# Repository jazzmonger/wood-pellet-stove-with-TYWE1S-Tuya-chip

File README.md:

Wood Pellet Stove with Tuya TYWE1S chip flashed with ESPHome gives you COMPLETE local control over ALL stove functions (and adds some).

> **No soldering, no flashing, no stove downtime:** if you just want local Home Assistant control (power, set temp, P1–P4, ECO1/ECO2, temperatures, decoded faults) without the vendor app, see **[docs/LOCAL-CONTROL.md](docs/LOCAL-CONTROL.md)**. It keeps the stock TYWE1S firmware and uses the [tuya-local](https://github.com/make-all/tuya-local) integration with the ready-made stove profile in [`tuya-local/`](tuya-local/pellet_stove_tywe1s.yaml). The ESPHome flashing and ESP32 mods below remain the way to unlock ultra-low burn, PID auger control, real-time temps and remote error reset.

The Discussions section also has LOTs of info: https://github.com/jazzmonger/wood-stove-with-TYWE1S-Tuya-chip/discussions
Including the discussion of a new circuit board design.

This project dives deep into the TuyaMCU parts of ESPHome that can be used to control various Tuya cloud based pellet stoves.  While the ESPHome TuyaMCU implementation is mostly robust, getting information on what it does and how it does it and why has been challenging to say the least.  I hope this helps someone else. I now have two of these stoves running ESPHome and FINALLY they function the way I want them to, not how some idiotic low-budget coder tried to program them.  I used to wake up cursing my pellet stoves.  Now I just wake up all warm and fuzzy.

The Advanced version completely replaces the Tuya Wifi module with an ESP32 D1 Mini chip and adds a whole new world of control to these stoves.

TuyaMCU Docs: https://esphome.io/components/tuya.html

The Tuya TYWE1S chips and those like it are basically just repackaged ESP8266 modules.  All the functions of the 8266 are all there.  The TuyaMCU libray in ESPHome provides an abstraction layer between the display/control module and Home Assistant. It allows control messages to be both Sent and Received from the device the module is controlling. In this case, our stove's main brain/control unit, or MCU as its called.

I'm an electronic engineer/designer by education and training, not a professional programmer, but thankfully ESPHome makes all this pretty easy. That said, I LOVE hacking this stuff, so  start with replacing the buggy, error prone Tuya control software by flashing ESPHome onto the display's TYE1S Tuya communications & controller chip.

**Product Models:** 
Cleveland Ironworks Wood Pellet Stove (there are 4 models, all use the same controller).  
https://www.cleveland-ironworks.com/products/pellet-stoves.html
I have a test bench set up with a spare control board. i have 2 models of this stove which both fail, but for different reasons.

It also appears from the Wifi module (N12210) that this exact same controller is used in Nemaxx Pellet Stove Pellet Heater P6 P9 P12.  https://www.ebay.com/itm/193755684864

Masterforge has the exact same models of this stove, all will use the same controller.

There are several others sold by Lowes, and other retailers that use the same display control board and TYWE1S chip.

There are a few displays that look slightly different but I believe all have the same basic internals. The displays have exactly the same function, just dufferent color faceplates. if they look like any of these then youre in luck!
All will have a TYWE1S chip that provide wifi functions that can be reprogrammed with ESPHome.

UPDATE: if the chip is the blue D1 Mini on the daughterboard, and the app you use is "Fire@home" and you got the stove in the EU, the stove uses the Blynk protocol, not Tuya.  We've exhausted all options trying to get this working. see the discussions. I would need the actual display board from this stove to decode the protocol being used

The wood stoves work ok some of the time, but the stove malfunctions fairly frequently.  
Common mafunctions include:
- randomly turning off w/ the msg "Goodbye!" on the display.
- pellets failing to light in the hopper
- not coming back on after power failure
- various cryptic E messages from time to time. E1,E2,ESC1, ESO1,ESC2,ESO2,etc  
- the stove will overheat when set to ECO2 and P1, throwing ESC1 errors. mitigate this with a fan behind the stove, triggered by exhaust temp.  set combustion fan to -10 for P1 in stove settings. 
Putting a fan behind the stove also fixes E6 error code indicating the temp sensor below the pellet hopper is reading too high

**Basic Problem Definition**
Pellet stoves made by Cleveland Ironworks all use the TuyaMCU chip TYWE1S to communicate with the stove's MCU inside the display unit.  Their shoddy programmer defined multiple datapoints for the same attribute in at least 2 cases, the most important being temperature.  This results in the Tuya integration reporting a random (usually negative) false value for current temp. The other problem is it sends its temp values as degrees F and ALL esphome climate entities originate in C.  If you set your HA instance to imperial, it will automagically convert C to F.  In this case it convering what it thinks is C ( but is really F) into F again.  temp readings are whacked and there was nothing you can do until now.

link to product manual https://www.cleveland-ironworks.com/mwdownloads/download/link/id/2763

Their app is a vendor written Tuya based app that looks like this:

Simply flashing esphome to the chip gives incorrect temp readings due to the stove using F instead of C for values. a fix for this is coming (update: its fixed).  The stove below might work great in purgatory (which, Im sure, is where these stoves were built), but not in the real world...

also, the main problem with trying to control the stove by brute force by manually controlling everything in ESPHome is setting your target temp doesn't work bc it fights with the stove's internal "set temp" that is set thru the front panel. when the room temp sensor reaches the user set value it shuts off to stove - its all a self contained system. The daughterbiard w/ the TYWE1S is only there to provide wifi support.  There there is no way to convert the stove control fully to to ESPHome. too many sensors, blowers, igniters, relays and safety issues to etc to deal with. This is all best left to the dusplay and main MCU control board. But we can secretly (and safely) intervene...

**Solution**
- Flash ESPHome to the TWYE1S daughterbiard chip using TuyaMCU. This is the module that normally relays info to and from the stoves control board and also provides a WiFi control interface to the Tuya iOT China based cloud platform. ESPHome eliiminates China from the equation and gives you local, Home Assistant control.
- use the new mod I got one of the ESPhome devs to make for me and you're golden.  its defined in the esphome config file.
- if your stove is turning off for no reason w/ "Goodbye" displayed on the screen, then the automations I've provided should help mitigate this
- go a step further and make a few *very* simple mods to the display and control board and you get FULL control over this stove WITHOUT sacraficing any of the safety features built into this stove.

See the Discussions for specific solutions to some of the errors and problems I've solved over the past year of doing battle with this stove. Its in the Discussions where I show the deep mods that are available and really make this Pellet Stove shine.

Post a message in the Discussions for basic questions or create a PR (problem report) if you are doing mods to your stove and run into issues.  I've tried to be as complete as possible and probably seen every problem these stoves have and then some.
Have fun!

**Data Points used by TuyaMCU and Tuya cloud:**
```
1 - Power on (Heat)
4 - Mode P1/P2/P3P4
101 - ECO1/ECO2
104 - Error Code
105 - random, unused
106 - Set desired room Temp
107 - Current Temp
108 - Pipe Temp
109 - Protect Temp
```
Error code is dp 104 (these come back from the server as numbers and are then mapped to error codes in the vendor app).  See my sensors.yaml file for how to decode them.

*Flashing the chip*
Carefully remove it from the display module.  It unplugs easily. or leave it in the display and use the power from the display to power the chip.  Ive done it both ways, either is fine.

this link shows you how to do it: https://tasmota.github.io/docs/TuyaMCU-Devices/#costco-charging-essentials

EDIT: for future reference, if unplugging the module from the display, I used 3.3v from the FTTD adapter to power the TYWE1S, U0TX (goes to RX on the FTTD adapter)  and U0RX (goes to TX on the FTTD adapter) then I only grounded GPIO0 at bootup to flash the chip.  Remove this ground from GPIO0 after its flashed and restart the chip. Also, connect 3.3V (not 5v) to the 3V3 pin on the TYWE1S chip, pin 4, or just leave the module plugged in and use the stove to power the chip.

WARNING - be careful when you solder wires to the board/chip to flash the chip.  I used breadbord wires w/pins and my VCC connection broke at some point and it took most of the circuit board trace off both the board AND the chip.  I salvaged it with a Frankenstein jumper, but you've been warned! Just be careful when handlin, use long wires and you should be fine.

The spiffy new entity with options to change Power and ECO mode. See the file uploads for all the code to generate these.

Special cards used frim HACS
type: custom:slider-entity-row
type: custom:plotly-graph

My "Ultimate" Pellet Stove Command Module after completely replacing the wifi module and Tuya chip with an ESP32 D1 mini. Yes, it can be done.

Another piece of the puzzle was to snoop on the RX UART line going from the display to the MCU control board.  this lets you echo messages from the display to home assistant as there is no other way to do it. its a little flakey at times (its just display messages), but mostly works. See the discussions section on how i achieved this bit of UART magic!

And finally, while i have had the stove burn for 2-3 days straight, it does go out if the ultra-low burn pot settings arent just right.  So, in the "Ultimate vesion" I add a wire to monitor the UART messages from the main MCU that contain temp updates so I can measure realtime temp updates (instead of at 1 min intervals via the Tuya crap). This helps to better control the burn pot and keep the fire from going out when on "Ultra Low" setting. Again, see Discussions for more info.

Build and use at your own risk!

I will not be responsible for any damages including but not limited to: errors or omissions, loss of life, or property damage. You have been warned.

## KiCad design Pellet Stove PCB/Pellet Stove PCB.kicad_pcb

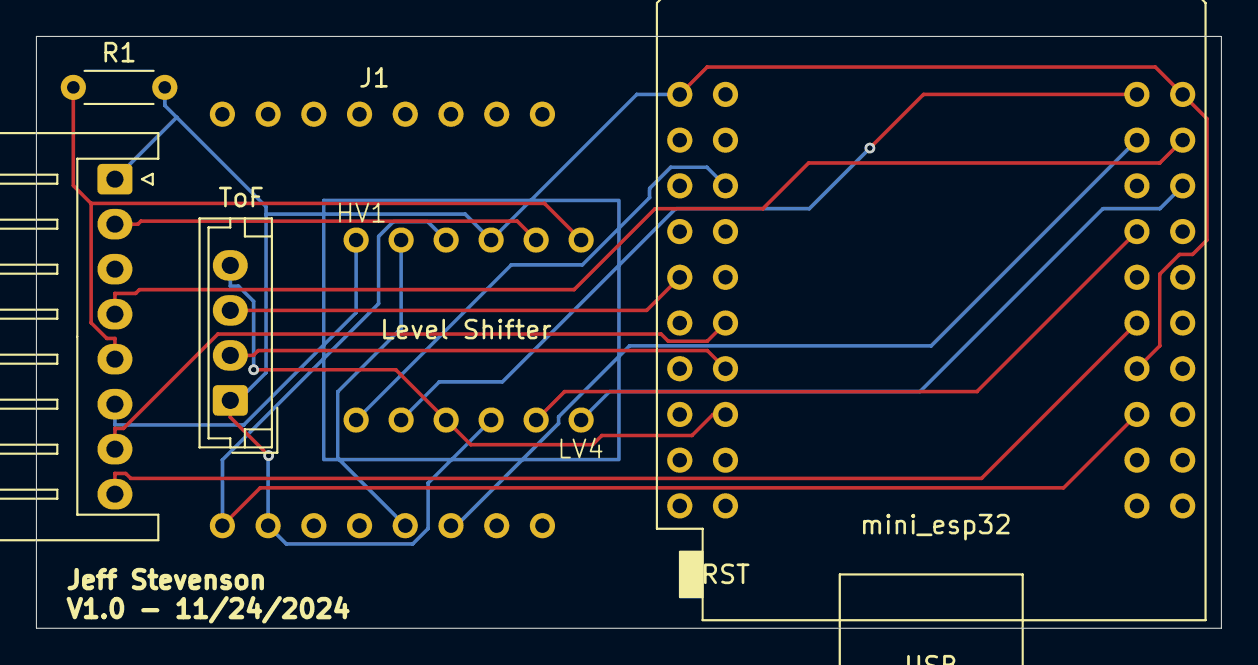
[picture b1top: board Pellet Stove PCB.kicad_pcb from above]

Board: 2 copper layers, 65.8 x 32.9 mm, 6 parts (0 on the bottom side), 17 nets.

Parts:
J1: Pellet Stove Header pins
J2: Logic Level Converter
J4: MCU USB & display; JST_XH_S8B-XH-A_1x08_P2.50mm_Horizontal
J6: ToF; JST_EH_B4B-EH-A_1x04_P2.50mm_Vertical
R1: 1k; R_Axial_DIN0204_L3.6mm_D1.6mm_P5.08mm_Horizontal
U1: mini_esp32; ESP32_mini

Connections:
GND: J1.10, J2.4 (GND), J2.9 (GND), J4.1, J6.1, R1.2, U1.1 (GND), U1.22 (GND), U1.33 (GND)
unnamed: J2.3 (3.3v), J6.4, U1.16 (3V3)
unnamed: J2.12 (HV1), J4.6
unnamed: J1.13, J2.11 (HV2)
unnamed: J2.8 (HV3), J4.2
unnamed: J2.7 (HV4), J4.5, R1.1
unnamed: J1.9, J2.10 (HV), U1.35 (VCC_(USB))
unnamed: J2.1 (LV1), U1.6 (IO_26/D0)
unnamed: J2.2 (LV2), U1.21 (TXD)
unnamed: J2.5 (LV3), U1.27 (IO_21/D2/SDA)
unnamed: J2.6 (LV4), U1.26 (IO_25)
unnamed: J4.4, U1.24 (IO_27)
unnamed: J4.7, U1.12 (IO_23/D7)
unnamed: J4.8, U1.31 (IO_16/D4)
unnamed: J6.2, U1.14 (IO_05/D8)
unnamed: J6.3, U1.9 (IO_33)
unnamed: J1.14, U1.23 (RXD)

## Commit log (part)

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2022-12-06 Add files via upload
    Various automations to add functionality to the pellet stove.
2022-12-06 Add files via upload
    Sensor.yaml file containing sensor definitions referenced in automations and Lovelace cards
2022-12-06 Add files via upload
    Cards to display pellet stove and debug all aspects
2022-12-21 Add files via upload
    Modifications to add new P5 power level that modifies Auger feed rates. Requires modifying both the display board and MCU board
2022-12-22 README File
2022-12-23 Adds new Power Level 5. NOTE: requires mods to MCU board
    config file that adds a Power Level P5 that is fully configurable while in ECO2 mode.
    The hope is this will turn down the heat slightly so the stove goes thru fewer on/off cycles and just maintains a heat adjust so the room just cools slightly. ECO2 mode will kick back to "Heating" wh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
    Requires MCU and Display board simple mod. See discussions
2022-12-23 adds sensors for wood pellet stove
2022-12-23 Various automations to manage pellet stove. names will need changing!
    I have 3 of these stoves, one dev, house, shop. my dev stove is on my workbench.
2023-01-11 Add files via upload
    #adds a Power Level P5 that is fully configurable while in ECO2 mode.
    #adds echo of actual display messages and status via MCU UART monitoring
    #
    #These mods will turn down the heat slightly during idle mode so the stove goes thru fewer
    #on/off cycles and just maintains a lower heat setting
    #so the room just cools slightly. when room cools, ECO2 mode will kick back to "Heating" which
2023-01-11 New power level P5. REQUIRES MODS!
    #adds a Power Level P5 that is fully configurable while in ECO2 mode.
    #adds echo of actual display messages and status via MCU UART monitoring
    #
    #These mods will turn down the heat slightly during idle mode so the stove goes thru fewer
    #on/off cycles and just maintains a lower heat setting
    #so the room just cools slightly. when room cools, ECO2 mode will kick back to "Heating" which
2023-01-21 Latest files
2023-01-21 Create new power level P5. Requires mods to Display/control bd
2023-01-28 Update and rename lovelace cards.yaml to lovelace cards(with all mods).yaml
    You need all my mods for these cards to function
2023-01-28 Basic Pellet Stove Lovelace card
    Use this with basic pellet stove , no physical mods.
    All Sensor names assume you use the following naming conventions in ESPHome config file:
    substitutions:
    device_name: "house-wood-pellet-stove"
    device_description: House Wood Pellet Stove running ESPHome
    friendly_name: House Wood Pellet Stove
2023-01-28 Basic Lovelace Pellet stove card (no mods)
2023-01-28 Lovelace card (with all physical stove mods)
    You must do all physical mods to the stove for these cards to work
2023-01-28 Various basic pellet stove automations
2023-01-28 Basic ESPHome config file (no physical mods)
2023-01-28 Pellet Stove Sensor entries
    Add these sensors to your sensor.yaml file
2023-01-28 configuration.yaml entries for binary_sensors
    add these binary sensors to your configuration.yaml file
2023-03-17 D1 Mini ESP32 firmware replaces entire Wifi daughter board
2023-03-17 Lovelace Command Center Dashboard - ESP32 version
2023-03-17 Sensor.yaml entries for Pellet stove
2023-04-10 ESP32 chip replaces TYWE1S
    Plus this adds a TON of features
2024-11-23 Pellet Stove PC Board KiCad design files, Symbols & Footprints
2025-01-05 ESP32 Pellet Stove with mods.yaml
2025-01-05 not relevant
2025-01-05 Basic ESPHome config file for wood pellet stove.yaml
2025-02-17 PID Version of Ultimate contoller.
    PID Version of Ultimate contoller.
2025-02-17 PID version of Modified Pellet Stove
    Auger mod on the main board is now corolled a low temps by a PID controller.
2025-11-02 Rename ESPHome config file for wood pellet stove.yaml to ESPHome basic config file fot TYWE1S chip flash.yaml
2025-11-15 Wood Pellet Stove Basic Config using ESP32
    Requires my pellet stove circuit board and an ESP32 to use this file
    # No mods to the pellet stove control board are required
    # Adds local sensors for all attributes previously in Tuya cloud
2025-11-15 sensor.yaml entries for home assistant
2025-11-15 ESP32 Pel. Stove with mods - PID Version.yaml
2025-11-15 ESPHome basic config file for TYWE1S chip flash.yaml to ESPHome basic config for TYWE1S chip flash.yaml
2025-11-15 configuration.yaml additions
2025-11-16 No mods with esp32 basic config & my circuit board
    Basic replacement of TYWE1S with my circuit & circuit board. No mods necessary.
2025-11-16 v4.1 ESP32 Pellet Stove with mods.yaml
2025-11-16 v4.1 ESP32 Pellet Stove with PID - requires mods.yaml
2025-11-16 ESPHome basic config for TYWE1S chip flash.yaml
2025-11-16 v 2.0 ESPHome basic config for TYWE1S chip flash.yaml
2025-12-01 Rename v4.1 ESP32 Pellet Stove with mods.yaml to v4.2 ESP32 Pellet Stove with mods.yaml
2025-12-30 Add Sensor for Exhaust and protect datapoint
